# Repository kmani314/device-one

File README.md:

# 明方電気 device one

The **device one** is a 60% mechanical keyboard kit that  contains two PCBs, mounting hardware, 3D-printed feet, and anti-skid  inserts. The PCB has a USB-C connector and supports ANSI, ISO,  split-backspace, split-shift, and arrow key layouts. It is programmable  using the open-source QMK software.

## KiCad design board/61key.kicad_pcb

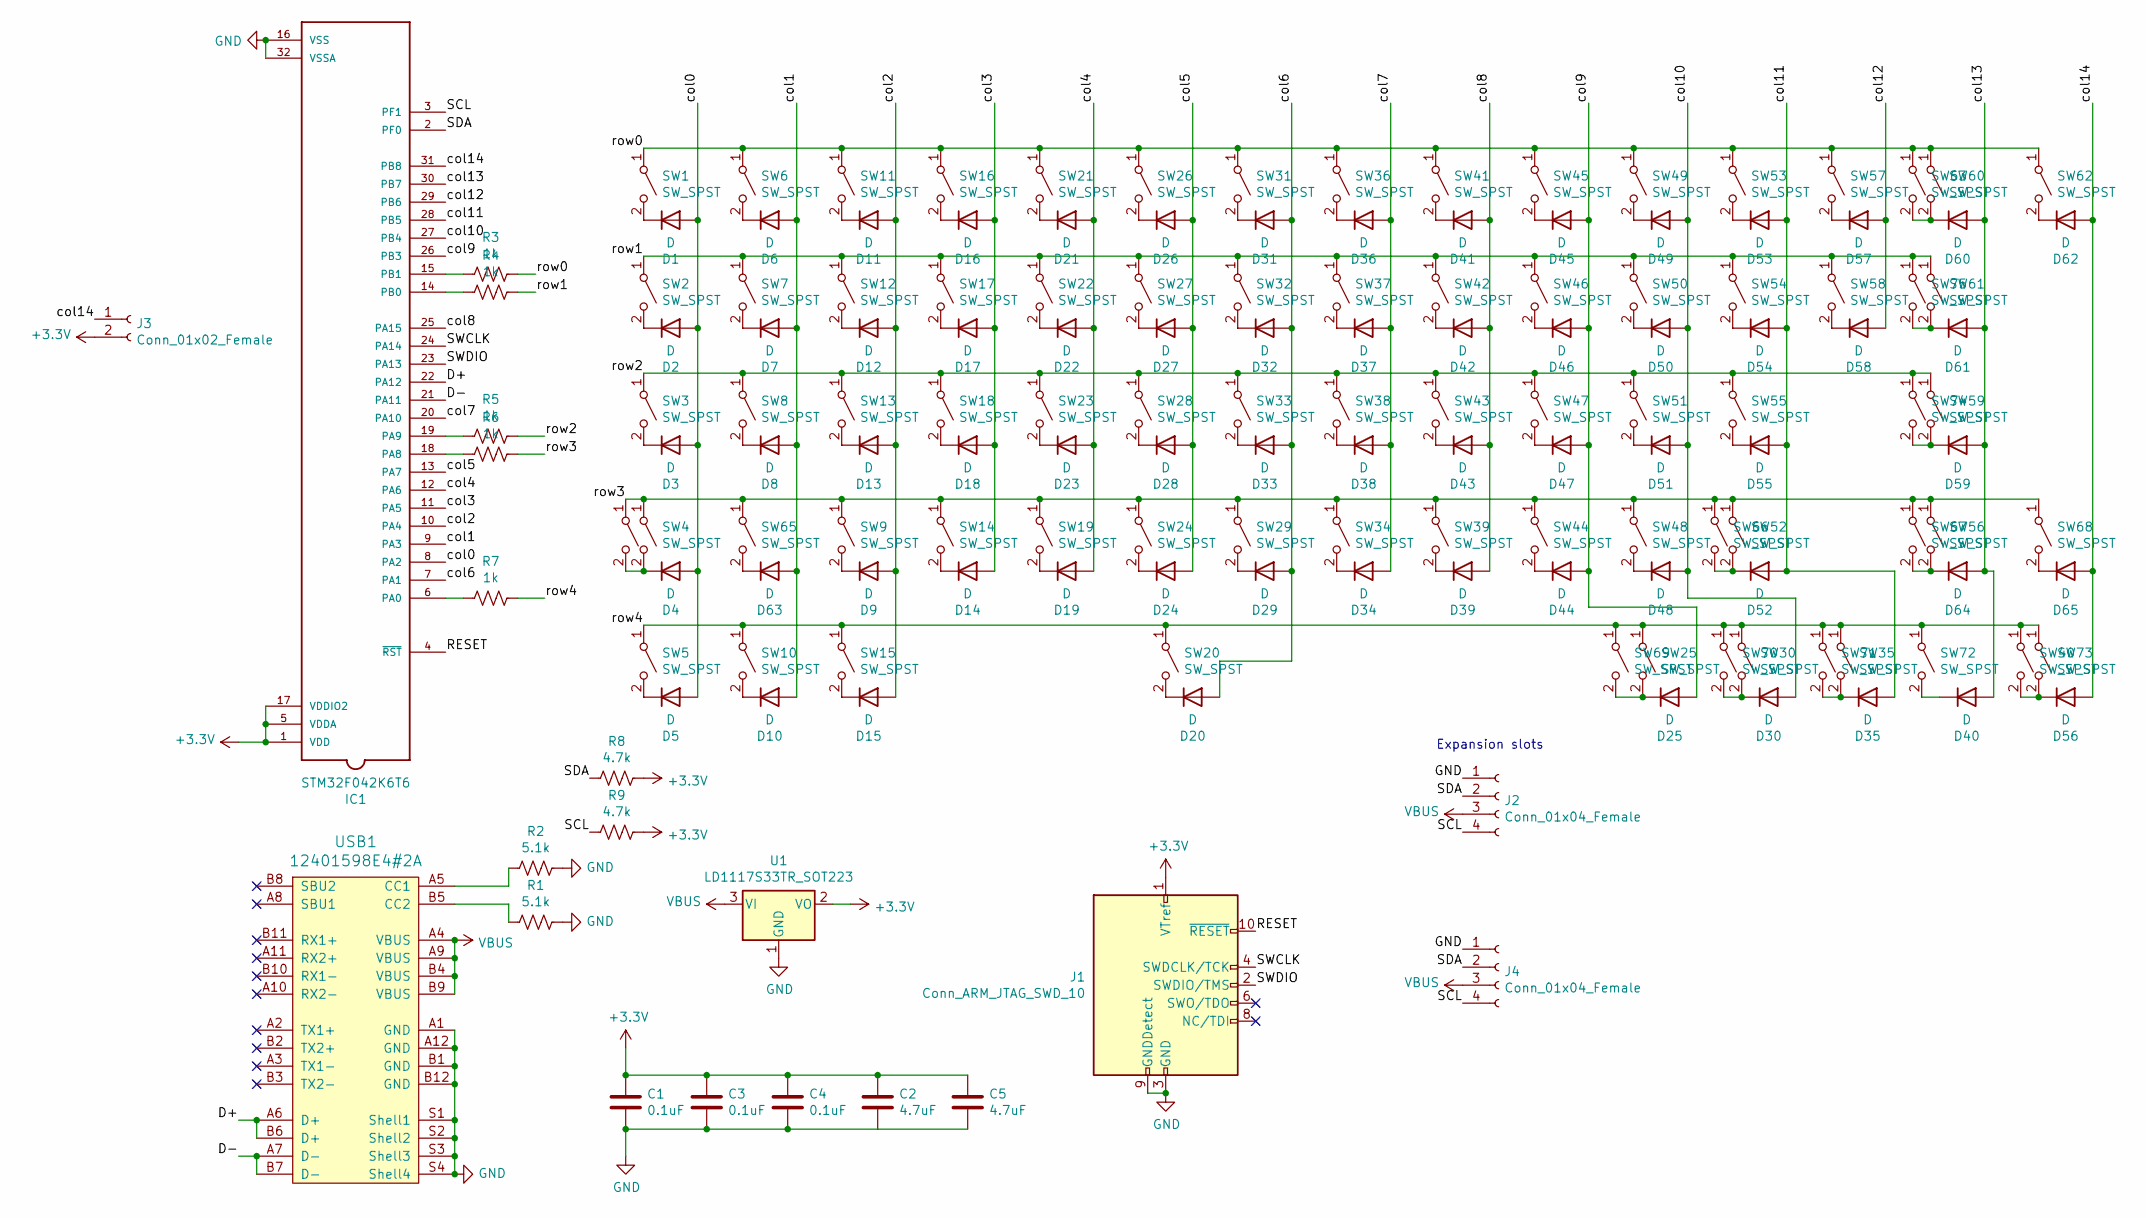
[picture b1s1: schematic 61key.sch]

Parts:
C1, C3, C4: 0.1uF; C_0603_1608Metric
C2, C5: 4.7uF; C_0603_1608Metric
D1, D2, D3, D4, D5, D6, D7, D8, D9, D10, D11, D12, D13, D14, D15, D16, D17, D18, D19, D20, D21, D22, D23, D24, D25, D26, D27, D28, D29, D30, D31, D32, D33, D34, D35, D36, D37, D38, D39, D40, D41, D42, D43, D44, D45, D46, D47, D48, D49, D50, D51, D52, D53, D54, D55, D56, D57, D58, D59, D60, D61, D62, D63, D64, D65: D; D_SOD-123F
IC1: STM32F042K6T6; QFP80P900X900X160-32N
J1: Conn_ARM_JTAG_SWD_10; PinHeader_2x05_P2.54mm_Vertical
J2, J4: Conn_01x04_Female; exp_header
J3: Conn_01x02_Female; PinHeader_1x02_P2.54mm_Vertical
R1, R2: 5.1k; R_0603_1608Metric
R3, R4, R5, R6, R7: 1k; R_0603_1608Metric
R8, R9: 4.7k; R_0603_1608Metric
SW1, SW2, SW3, SW4, SW5, SW6, SW7, SW8, SW9, SW10, SW11, SW12, SW13, SW14, SW15, SW16, SW17, SW18, SW19, SW20, SW21, SW22, SW23, SW24, SW25, SW26, SW27, SW28, SW29, SW30, SW31, SW32, SW33, SW34, SW35, SW36, SW37, SW38, SW39, SW40, SW41, SW42, SW43, SW44, SW45, SW46, SW47, SW48, SW49, SW50, SW51, SW52, SW53, SW54, SW55, SW56, SW57, SW58, SW59, SW60, SW61, SW62, SW63, SW64, SW65, SW66, SW67, SW68, SW69, SW70, SW71, SW72, SW73, SW74, SW75: SW_SPST; SW_MX
U1: LD1117S33TR_SOT223; SOT-223-3_TabPin2
USB1: 12401598E4#2A; HRO-TYPE-C-31-M-12

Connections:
+3V3: C1.1, C2.1, C3.1, C4.1, C5.1, IC1.1 (VDD), IC1.5 (VDDA), IC1.17 (VDDIO2), J1.1 (VTref), J3.2, R8.1, R9.1, U1.2 (VO)
/D+: IC1.22 (PA12), USB1.A6 (D+), USB1.B6 (D+)
/D-: IC1.21 (PA11), USB1.A7 (D-), USB1.B7 (D-)
/RESET: IC1.4 (~RST~), J1.10 (~RESET~)
/SCL: IC1.3 (PF1), J2.4, J4.4, R9.2
/SDA: IC1.2 (PF0), J2.2, J4.2, R8.2
/SWCLK: IC1.24 (PA14), J1.4 (SWDCLK/TCK)
/SWDIO: IC1.23 (PA13), J1.2 (SWDIO/TMS)
/col0: D1.2 (A), D2.2 (A), D3.2 (A), D4.2 (A), D5.2 (A), IC1.8 (PA2)
/col1: D6.2 (A), D7.2 (A), D8.2 (A), D10.2 (A), D63.2 (A), IC1.9 (PA3)
/col2: D9.2 (A), D11.2 (A), D12.2 (A), D13.2 (A), D15.2 (A), IC1.10 (PA4)
/col3: D14.2 (A), D16.2 (A), D17.2 (A), D18.2 (A), IC1.11 (PA5)
/col4: D19.2 (A), D21.2 (A), D22.2 (A), D23.2 (A), IC1.12 (PA6)
/col5: D24.2 (A), D26.2 (A), D27.2 (A), D28.2 (A), IC1.13 (PA7)
/col6: D20.2 (A), D29.2 (A), D31.2 (A), D32.2 (A), D33.2 (A), IC1.7 (PA1)
/col7: D34.2 (A), D36.2 (A), D37.2 (A), D38.2 (A), IC1.20 (PA10)
/col8: D39.2 (A), D41.2 (A), D42.2 (A), D43.2 (A), IC1.25 (PA15)
/col9: D25.2 (A), D44.2 (A), D45.2 (A), D46.2 (A), D47.2 (A), IC1.26 (PB3)
/col10: D30.2 (A), D48.2 (A), D49.2 (A), D50.2 (A), D51.2 (A), IC1.27 (PB4)
/col11: D35.2 (A), D52.2 (A), D53.2 (A), D54.2 (A), D55.2 (A), IC1.28 (PB5)
/col12: D57.2 (A), D58.2 (A), IC1.29 (PB6)
/col13: D40.2 (A), D59.2 (A), D60.2 (A), D61.2 (A), D64.2 (A), IC1.30 (PB7)
/col14: D56.2 (A), D62.2 (A), D65.2 (A), IC1.31 (PB8), J3.1
/row0: R3.1, SW1.1 (A), SW6.1 (A), SW11.1 (A), SW16.1 (A), SW21.1 (A), SW26.1 (A), SW31.1 (A), SW36.1 (A), SW41.1 (A), SW45.1 (A), SW49.1 (A), SW53.1 (A), SW57.1 (A), SW60.1 (A), SW62.1 (A), SW63.1 (A)
/row1: R4.1, SW2.1 (A), SW7.1 (A), SW12.1 (A), SW17.1 (A), SW22.1 (A), SW27.1 (A), SW32.1 (A), SW37.1 (A), SW42.1 (A), SW46.1 (A), SW50.1 (A), SW54.1 (A), SW58.1 (A), SW61.1 (A), SW75.1 (A)
/row2: R5.1, SW3.1 (A), SW8.1 (A), SW13.1 (A), SW18.1 (A), SW23.1 (A), SW28.1 (A), SW33.1 (A), SW38.1 (A), SW43.1 (A), SW47.1 (A), SW51.1 (A), SW55.1 (A), SW59.1 (A), SW74.1 (A)
/row3: R6.1, SW4.1 (A), SW9.1 (A), SW14.1 (A), SW19.1 (A), SW24.1 (A), SW29.1 (A), SW34.1 (A), SW39.1 (A), SW44.1 (A), SW48.1 (A), SW52.1 (A), SW56.1 (A), SW64.1 (A), SW65.1 (A), SW66.1 (A), SW67.1 (A), SW68.1 (A)
/row4: R7.1, SW5.1 (A), SW10.1 (A), SW15.1 (A), SW20.1 (A), SW25.1 (A), SW30.1 (A), SW35.1 (A), SW40.1 (A), SW69.1 (A), SW70.1 (A), SW71.1 (A), SW72.1 (A), SW73.1 (A)
GND: C1.2, C2.2, C3.2, C4.2, C5.2, IC1.16 (VSS), IC1.32 (VSSA), J1.3 (GND), J1.5 (GND), J1.9 (GNDDetect), J2.1, J4.1, R1.1, R2.1, U1.1 (GND), USB1.A1 (GND), USB1.A12 (GND), USB1.B1 (GND), USB1.B12 (GND), USB1.S1 (Shell1), USB1.S2 (Shell2), USB1.S3 (Shell3), USB1.S4 (Shell4)
unnamed: D1.1 (K), SW1.2 (B)
unnamed: D2.1 (K), SW2.2 (B)
unnamed: D3.1 (K), SW3.2 (B)
unnamed: D4.1 (K), SW4.2 (B), SW64.2 (B)
unnamed: D5.1 (K), SW5.2 (B)
unnamed: D6.1 (K), SW6.2 (B)
unnamed: D7.1 (K), SW7.2 (B)
unnamed: D8.1 (K), SW8.2 (B)
unnamed: D9.1 (K), SW9.2 (B)
unnamed: D10.1 (K), SW10.2 (B)
unnamed: D11.1 (K), SW11.2 (B)
unnamed: D12.1 (K), SW12.2 (B)
unnamed: D13.1 (K), SW13.2 (B)
unnamed: D14.1 (K), SW14.2 (B)
unnamed: D15.1 (K), SW15.2 (B)
unnamed: D16.1 (K), SW16.2 (B)
unnamed: D17.1 (K), SW17.2 (B)
unnamed: D18.1 (K), SW18.2 (B)
unnamed: D19.1 (K), SW19.2 (B)
unnamed: D20.1 (K), SW20.2 (B)
unnamed: D21.1 (K), SW21.2 (B)
unnamed: D22.1 (K), SW22.2 (B)
unnamed: D23.1 (K), SW23.2 (B)
unnamed: D24.1 (K), SW24.2 (B)
unnamed: D25.1 (K), SW25.2 (B), SW69.2 (B)
unnamed: D26.1 (K), SW26.2 (B)
unnamed: D27.1 (K), SW27.2 (B)
unnamed: D28.1 (K), SW28.2 (B)
unnamed: D29.1 (K), SW29.2 (B)
unnamed: D30.1 (K), SW30.2 (B), SW70.2 (B)
unnamed: D31.1 (K), SW31.2 (B)
unnamed: D32.1 (K), SW32.2 (B)
unnamed: D33.1 (K), SW33.2 (B)
unnamed: D34.1 (K), SW34.2 (B)
unnamed: D35.1 (K), SW35.2 (B), SW71.2 (B)
unnamed: D36.1 (K), SW36.2 (B)
unnamed: D37.1 (K), SW37.2 (B)
unnamed: D38.1 (K), SW38.2 (B)
unnamed: D39.1 (K), SW39.2 (B)
unnamed: D40.1 (K), SW72.2 (B)
unnamed: D41.1 (K), SW41.2 (B)
unnamed: D42.1 (K), SW42.2 (B)
unnamed: D43.1 (K), SW43.2 (B)
unnamed: D44.1 (K), SW44.2 (B)
unnamed: D45.1 (K), SW45.2 (B)
unnamed: D46.1 (K), SW46.2 (B)
unnamed: D47.1 (K), SW47.2 (B)
unnamed: D48.1 (K), SW48.2 (B)
unnamed: D49.1 (K), SW49.2 (B)
unnamed: D50.1 (K), SW50.2 (B)
unnamed: D51.1 (K), SW51.2 (B)
unnamed: D52.1 (K), SW52.2 (B), SW66.2 (B)
unnamed: D53.1 (K), SW53.2 (B)
unnamed: D54.1 (K), SW54.2 (B)
unnamed: D55.1 (K), SW55.2 (B)
unnamed: D56.1 (K), SW40.2 (B), SW73.2 (B)
unnamed: D57.1 (K), SW57.2 (B)
unnamed: D58.1 (K), SW58.2 (B)
unnamed: D59.1 (K), SW59.2 (B), SW74.2 (B)
unnamed: D60.1 (K), SW60.2 (B), SW63.2 (B)
unnamed: D61.1 (K), SW61.2 (B), SW75.2 (B)
unnamed: D62.1 (K), SW62.2 (B)
unnamed: D63.1 (K), SW65.2 (B)
unnamed: D64.1 (K), SW56.2 (B), SW67.2 (B)
unnamed: D65.1 (K), SW68.2 (B)
unnamed: IC1.6 (PA0), R7.2
unnamed: IC1.14 (PB0), R4.2
unnamed: IC1.15 (PB1), R3.2
unnamed: IC1.18 (PA8), R6.2
unnamed: IC1.19 (PA9), R5.2
unnamed: R1.2, USB1.B5 (CC2)
unnamed: R2.2, USB1.A5 (CC1)
VBUS: J2.3, J4.3, U1.3 (VI), USB1.A4 (VBUS), USB1.A9 (VBUS), USB1.B4 (VBUS), USB1.B9 (VBUS)

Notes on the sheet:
Expansion slots

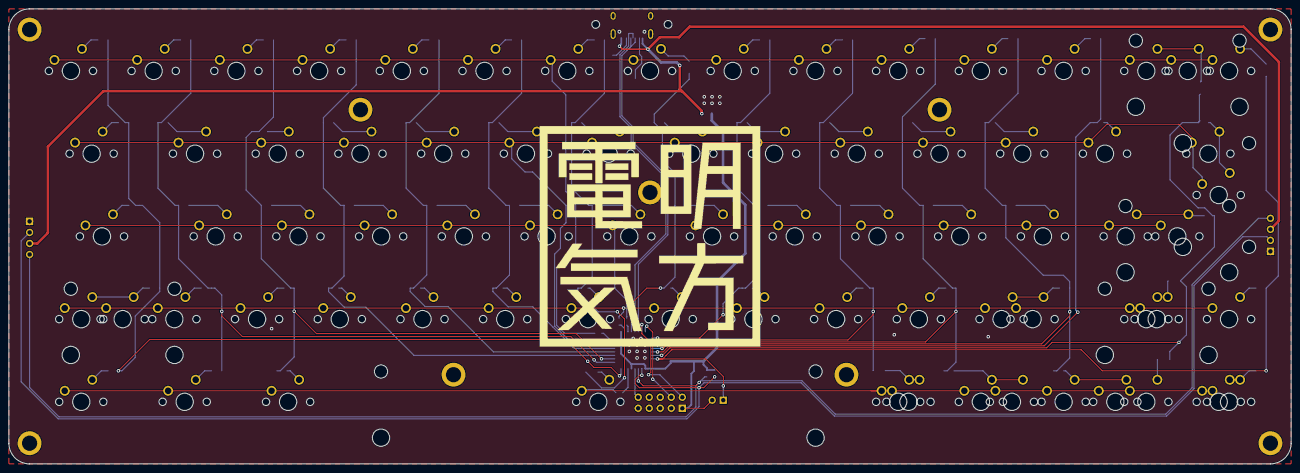
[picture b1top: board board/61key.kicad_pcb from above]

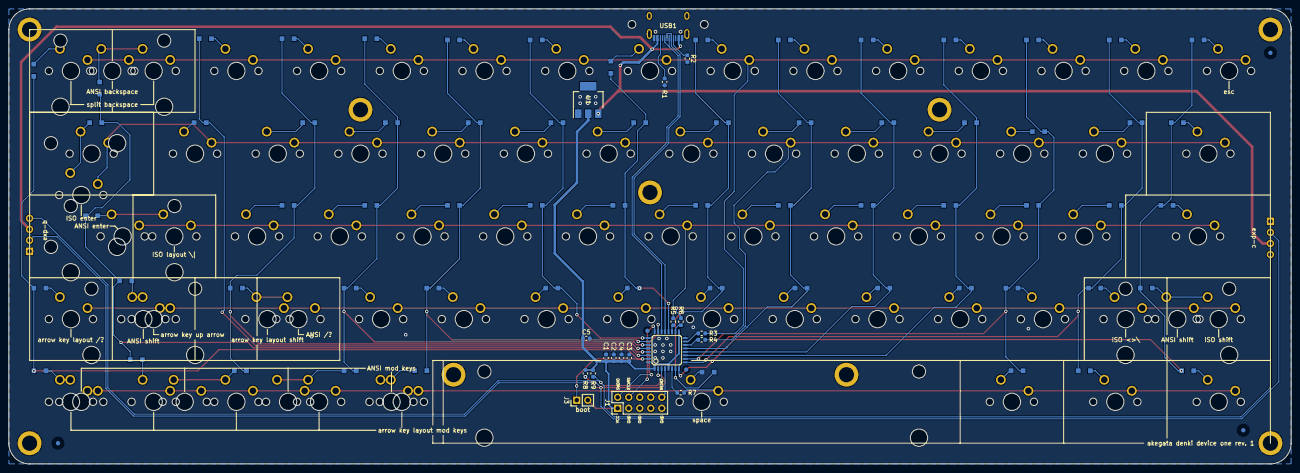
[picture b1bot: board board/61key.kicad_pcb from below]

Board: 2 copper layers, 295.3 x 104.8 mm, 172 parts (89 on the bottom side), 102 nets.

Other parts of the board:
>NAME: >VALUE; MX_STAB_6.75U
>NAME#2: >VALUE; MX_STAB_2.75U
>NAME#3, >NAME#4: >VALUE; MX_STAB_2.25U
F1, F4, F5: Fiducial_1mm_Mask3mm
F2, F3: Fiducial_1mm_Mask2mm
ST72, ST72#2: Stabilizer; MX_STAB_2U

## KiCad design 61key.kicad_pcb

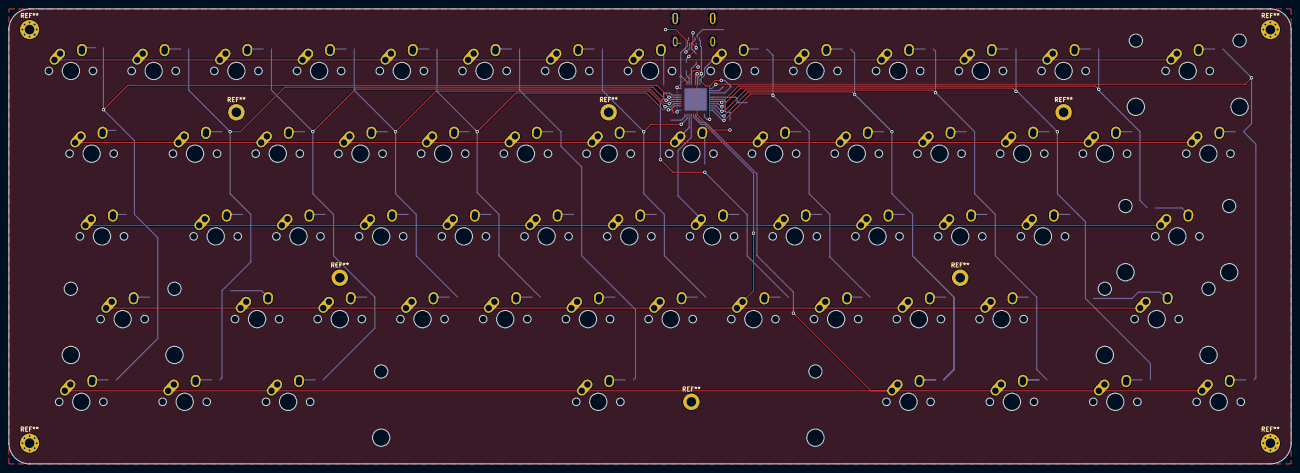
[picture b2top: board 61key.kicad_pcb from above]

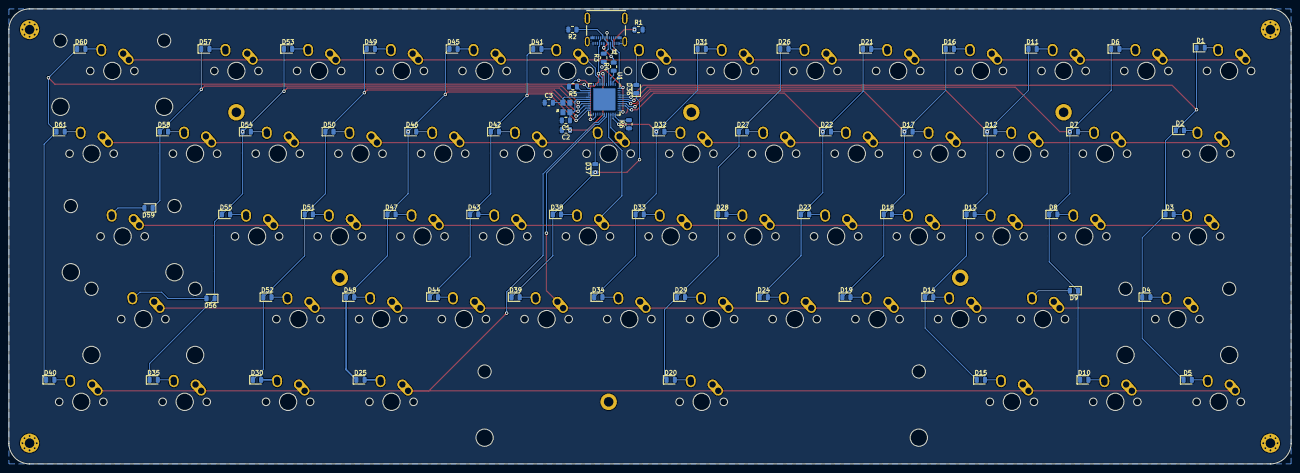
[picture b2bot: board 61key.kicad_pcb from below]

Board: 2 copper layers, 295.3 x 104.8 mm, 134 parts (73 on the bottom side), 93 nets.

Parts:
C1, C2, C3: C; C_0805_2012Metric
D1, D2, D3, D4, D5, D6, D7, D8, D9, D10, D11, D12, D13, D14, D15, D16, D17, D18, D19, D20, D21, D22, D23, D24, D25, D26, D27, D28, D29, D30, D31, D32, D33, D34, D35, D36, D37, D38, D39, D40, D41, D42, D43, D44, D45, D46, D47, D48, D49, D50, D51, D52, D53, D54, D55, D56, D57, D58, D59, D60, D61: D; D_0805_2012Metric
J1: 105450-0101; MOLEX_105450-0101
R1, R2, R3, R4, R5, R6: R_US; R_0805_2012Metric
SW1, SW6, SW7, SW8, SW9, SW11, SW12, SW13, SW14, SW16, SW17, SW18, SW19, SW21, SW22, SW23, SW24, SW26, SW27, SW28, SW29, SW31, SW32, SW33, SW34, SW36, SW37, SW38, SW39, SW41, SW42, SW43, SW44, SW45, SW46, SW47, SW48, SW49, SW50, SW51, SW52, SW53, SW54, SW55, SW57, SW58: SW_SPST; MX-1U-NoLED
SW2, SW61: SW_SPST; MX-1.5U-NoLED
SW3: SW_SPST; MX-1.75U-NoLED
SW4, SW59: SW_SPST; MX-2.25U-NoLED
SW5, SW10, SW15, SW25, SW30, SW35, SW40: SW_SPST; MX-1.25U-NoLED
SW20: SW_SPST; MX-6.25U-NoLED
SW56: SW_SPST; MX-2.75U-NoLED
SW60: SW_SPST; MX-2U-NoLED
U1: ATmega32U4-AU; QFN-44-1EP_7x7mm_Pitch0.5mm
X1: FA-238; OSCCC320X250X70-4N

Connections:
/RESET: R5.1, U1.13
/col0: D1.1, D2.1, D3.1, D4.1, D5.1, U1.40
/col1: D6.1, D7.1, D8.1, D9.1, D10.1, U1.39
/col2: D11.1, D12.1, D13.1, D14.1, D15.1, U1.38
/col3: D16.1, D17.1, D18.1, D19.1, U1.37
/col4: D21.1, D22.1, D23.1, D24.1, U1.36
/col5: D20.1, D26.1, D27.1, D28.1, D29.1
/col6: D31.1, D32.1, D33.1, D34.1, U1.32
/col7: D36.1, D37.1, D38.1, D39.1, U1.41
/col8: D41.1, D42.1, D43.1, D44.1, U1.22
/col9: D25.1, D45.1, D46.1, D47.1, D48.1, U1.21
/col10: D30.1, D49.1, D50.1, D51.1, D52.1, U1.20
/col11: D35.1, D53.1, D54.1, D55.1, D56.1, U1.19
/col12: D57.1, D58.1, D59.1, U1.18
/col13: D40.1, D60.1, D61.1, U1.12
/row0: SW1.1, SW6.1, SW11.1, SW16.1, SW21.1, SW26.1, SW31.1, SW36.1, SW41.1, SW45.1, SW49.1, SW53.1, SW57.1, SW60.1, U1.8
/row1: SW2.1, SW7.1, SW12.1, SW17.1, SW22.1, SW27.1, SW32.1, SW37.1, SW42.1, SW46.1, SW50.1, SW54.1, SW58.1, SW61.1, U1.31
/row2: SW3.1, SW8.1, SW13.1, SW18.1, SW23.1, SW28.1, SW33.1, SW38.1, SW43.1, SW47.1, SW51.1, SW55.1, SW59.1, U1.30
/row3: SW4.1, SW9.1, SW14.1, SW19.1, SW24.1, SW29.1, SW34.1, SW39.1, SW44.1, SW48.1, SW52.1, SW56.1, U1.29
/row4: SW5.1, SW10.1, SW15.1, SW20.1, SW25.1, SW30.1, SW35.1, SW40.1, U1.28
GND: C1.2, C2.2, C3.1, J1.A1, J1.A12, J1.B1, J1.B12, J1.S1, J1.S2, J1.S3, J1.S4, R1.2, R2.2, R6.1, U1.5, U1.15, U1.23, U1.35, U1.43, X1.2, X1.4
unnamed: C1.1, U1.17, X1.1
unnamed: C2.1, U1.6
unnamed: C3.2, U1.16, X1.3
unnamed: D1.2, SW1.2
unnamed: D2.2, SW2.2
unnamed: D3.2, SW3.2
unnamed: D4.2, SW4.2
unnamed: D5.2, SW5.2
unnamed: D6.2, SW6.2
unnamed: D7.2, SW7.2
unnamed: D8.2, SW8.2
unnamed: D9.2, SW9.2
unnamed: D10.2, SW10.2
unnamed: D11.2, SW11.2
unnamed: D12.2, SW12.2
unnamed: D13.2, SW13.2
unnamed: D14.2, SW14.2
unnamed: D15.2, SW15.2
unnamed: D16.2, SW16.2
unnamed: D17.2, SW17.2
unnamed: D18.2, SW18.2
unnamed: D19.2, SW19.2
unnamed: D20.2, SW20.2
unnamed: D21.2, SW21.2
unnamed: D22.2, SW22.2
unnamed: D23.2, SW23.2
unnamed: D24.2, SW24.2
unnamed: D25.2, SW25.2
unnamed: D26.2, SW26.2
unnamed: D27.2, SW27.2
unnamed: D28.2, SW28.2
unnamed: D29.2, SW29.2
unnamed: D30.2, SW30.2
unnamed: D31.2, SW31.2
unnamed: D32.2, SW32.2
unnamed: D33.2, SW33.2
unnamed: D34.2, SW34.2
unnamed: D35.2, SW35.2
unnamed: D36.2, SW36.2
unnamed: D37.2, SW37.2
unnamed: D38.2, SW38.2
unnamed: D39.2, SW39.2
unnamed: D40.2, SW40.2
unnamed: D41.2, SW41.2
unnamed: D42.2, SW42.2
unnamed: D43.2, SW43.2
unnamed: D44.2, SW44.2
unnamed: D45.2, SW45.2
unnamed: D46.2, SW46.2
unnamed: D47.2, SW47.2
unnamed: D48.2, SW48.2
unnamed: D49.2, SW49.2
unnamed: D50.2, SW50.2
unnamed: D51.2, SW51.2
unnamed: D52.2, SW52.2
unnamed: D53.2, SW53.2
unnamed: D54.2, SW54.2
unnamed: D55.2, SW55.2
unnamed: D56.2, SW56.2
unnamed: D57.2, SW57.2
unnamed: D58.2, SW58.2
unnamed: D59.2, SW59.2
unnamed: D60.2, SW60.2
unnamed: D61.2, SW61.2
unnamed: J1.A5, R1.1
unnamed: J1.A6, J1.B6, R3.2
unnamed: J1.A7, J1.B7, R4.2
unnamed: J1.B5, R2.1
unnamed: R3.1, U1.4
unnamed: R4.1, U1.3
unnamed: R6.2, U1.33
VCC: J1.A4, J1.A9, J1.B4, J1.B9, R5.2, U1.2, U1.7, U1.14, U1.24, U1.34, U1.44

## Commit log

2020-05-02 add gitattributes
2020-05-03 add footprints, finish basic schematic, working on pcb
2020-05-04 footprints, key arrangement, board dimensions
2020-05-05 basic pcb, issues with holes
2020-05-06 add step for renders
2020-05-06 optimize entire board
2020-05-07 clean up files, move things to their own directories
2020-05-07 add pads, new step
2020-05-07 add svg
2020-05-07 add board images, remove svg
2020-05-07 better img
2020-05-07 add better img and logo
2020-05-09 new images, backplate, clean up for smt assembly
2020-05-13 big overhaul
2020-05-14 layouts done, need to add traces
2020-05-15 rows and columns for all layouts done
2020-05-16 basic pcb done
2020-05-17 need to create models to check board compatibility; prototype candidate
2020-05-17 logos, gerber
2020-05-17 backplate fixes
2020-05-26 add svgs for stencil
2020-05-26 add dxf
2020-05-29 new images and steps
2020-06-13 cleanup
2020-06-21 update step file
2020-07-10 add readme
